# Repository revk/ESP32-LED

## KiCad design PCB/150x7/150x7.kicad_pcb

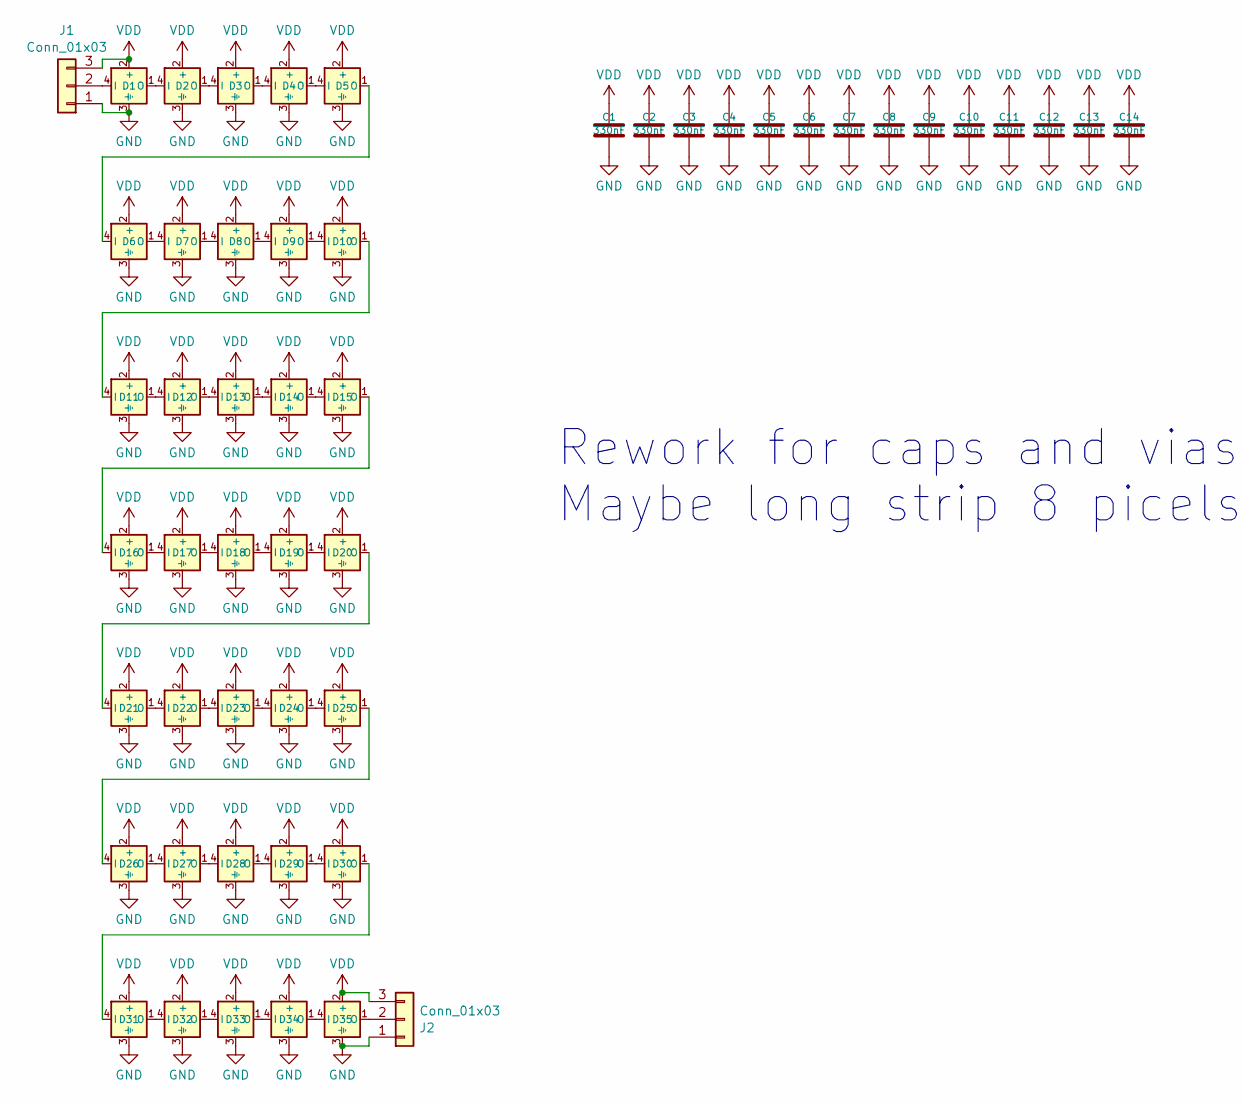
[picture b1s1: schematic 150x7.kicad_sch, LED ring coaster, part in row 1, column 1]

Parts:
C1, C2, C3, C4, C5, C6, C7, C8, C9, C10, C11, C12, C13, C14: 330nF; C_0402
D1, D2, D3, D4, D5, D6, D7, D8, D9, D10, D11, D12, D13, D14, D15, D16, D17, D18, D19, D20, D21, D22, D23, D24, D25, D26, D27, D28, D29, D30, D31, D32, D33, D34, D35: XL-1010RGBC-WS2812B; SMD1010; LCSC Part # C5349953
J1, J2: Conn_01x03; 3-PADS

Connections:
GND: C1.2, C2.2, C3.2, C4.2, C5.2, C6.2, C7.2, C8.2, C9.2, C10.2, C11.2, C12.2, C13.2, C14.2, D1.3 (⏚), D2.3 (⏚), D3.3 (⏚), D4.3 (⏚), D5.3 (⏚), D6.3 (⏚), D7.3 (⏚), D8.3 (⏚), D9.3 (⏚), D10.3 (⏚), D11.3 (⏚), D12.3 (⏚), D13.3 (⏚), D14.3 (⏚), D15.3 (⏚), D16.3 (⏚), D17.3 (⏚), D18.3 (⏚), D19.3 (⏚), D20.3 (⏚), D21.3 (⏚), D22.3 (⏚), D23.3 (⏚), D24.3 (⏚), D25.3 (⏚), D26.3 (⏚), D27.3 (⏚), D28.3 (⏚), D29.3 (⏚), D30.3 (⏚), D31.3 (⏚), D32.3 (⏚), D33.3 (⏚), D34.3 (⏚), D35.3 (⏚), J1.1, J2.1
unnamed: D1.4 (I), J1.2
unnamed: D1.1 (O), D2.4 (I)
unnamed: D2.1 (O), D3.4 (I)
unnamed: D3.1 (O), D4.4 (I)
unnamed: D4.1 (O), D5.4 (I)
unnamed: D5.1 (O), D6.4 (I)
unnamed: D6.1 (O), D7.4 (I)
unnamed: D7.1 (O), D8.4 (I)
unnamed: D8.1 (O), D9.4 (I)
unnamed: D9.1 (O), D10.4 (I)
unnamed: D10.1 (O), D11.4 (I)
unnamed: D11.1 (O), D12.4 (I)
unnamed: D12.1 (O), D13.4 (I)
unnamed: D13.1 (O), D14.4 (I)
unnamed: D14.1 (O), D15.4 (I)
unnamed: D15.1 (O), D16.4 (I)
unnamed: D16.1 (O), D17.4 (I)
unnamed: D17.1 (O), D18.4 (I)
unnamed: D18.1 (O), D19.4 (I)
unnamed: D19.1 (O), D20.4 (I)
unnamed: D20.1 (O), D21.4 (I)
unnamed: D21.1 (O), D22.4 (I)
unnamed: D22.1 (O), D23.4 (I)
unnamed: D23.1 (O), D24.4 (I)
unnamed: D24.1 (O), D25.4 (I)
unnamed: D25.1 (O), D26.4 (I)
unnamed: D26.1 (O), D27.4 (I)
unnamed: D27.1 (O), D28.4 (I)
unnamed: D28.1 (O), D29.4 (I)
unnamed: D29.1 (O), D30.4 (I)
unnamed: D30.1 (O), D31.4 (I)
unnamed: D31.1 (O), D32.4 (I)
unnamed: D32.1 (O), D33.4 (I)
unnamed: D33.1 (O), D34.4 (I)
unnamed: D34.1 (O), D35.4 (I)
unnamed: D35.1 (O), J2.2
VDD: C1.1, C2.1, C3.1, C4.1, C5.1, C6.1, C7.1, C8.1, C9.1, C10.1, C11.1, C12.1, C13.1, C14.1, D1.2 (+), D2.2 (+), D3.2 (+), D4.2 (+), D5.2 (+), D6.2 (+), D7.2 (+), D8.2 (+), D9.2 (+), D10.2 (+), D11.2 (+), D12.2 (+), D13.2 (+), D14.2 (+), D15.2 (+), D16.2 (+), D17.2 (+), D18.2 (+), D19.2 (+), D20.2 (+), D21.2 (+), D22.2 (+), D23.2 (+), D24.2 (+), D25.2 (+), D26.2 (+), D27.2 (+), D28.2 (+), D29.2 (+), D30.2 (+), D31.2 (+), D32.2 (+), D33.2 (+), D34.2 (+), D35.2 (+), J1.3, J2.3

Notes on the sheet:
Rework for caps and vias at top/bottom Maybe long strip 8 picels high to allow scrolling text

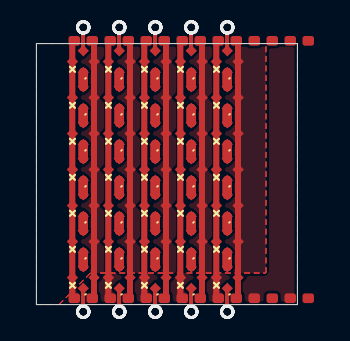
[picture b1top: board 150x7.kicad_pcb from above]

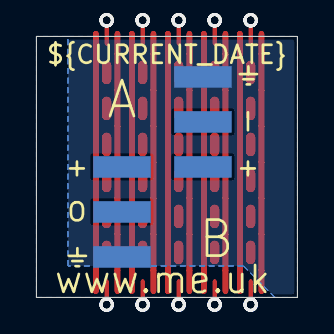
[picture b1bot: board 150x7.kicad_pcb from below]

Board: 2 copper layers, 14.5 x 14.5 mm, 51 parts (2 on the bottom side), 38 nets.

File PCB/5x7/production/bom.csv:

Designator,Footprint,Quantity,Value,LCSC Part #
"C1, C10, C2, C3, C4, C5, C6, C7, C8, C9",C_0402,10,330nF,
"D1, D10, D11, D12, D13, D14, D15, D16, D17, D18, D19, D2, D20, D21, D22, D23, D24, D25, D26, D27, D28, D29, D3, D30, D31, D32, D33, D34, D35, D4, D5, D6, D7, D8, D9",SMD1010,35,XL-1010RGBC-WS2812B,
"J1, J2",3-PADS,2,Conn_01x03,

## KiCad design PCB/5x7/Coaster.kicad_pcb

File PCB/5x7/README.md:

# 5x7

These files are for use in [KiCad](https://www.kicad.org).

## Trademark

This is an open source project, but bear in mind you cannot sell boards bearing the Andrews & Arnold Ltd name, the A&A logo, the registered trademark AJK logo, or the GS1 allocated EANs assigned to Andrews & Arnold Ltd.

## Images

*Auto generated 2025-08-12T11:30:27*

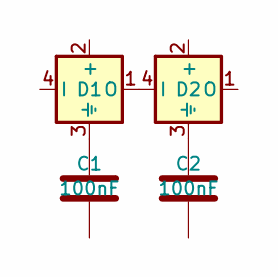
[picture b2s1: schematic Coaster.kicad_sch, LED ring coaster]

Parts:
C1, C2: 100nF; C_0201
D1, D2: XL-1010RGBC-WS2812B; SMD1010; LCSC Part # C5349953

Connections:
unnamed: D1.1 (O), D2.4 (I)
unnamed: C1.1, D1.3 (⏚)
unnamed: C2.1, D2.3 (⏚)

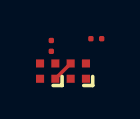
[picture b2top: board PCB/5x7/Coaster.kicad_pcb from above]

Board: 2 copper layers, 4 parts (0 on the bottom side), 3 nets.

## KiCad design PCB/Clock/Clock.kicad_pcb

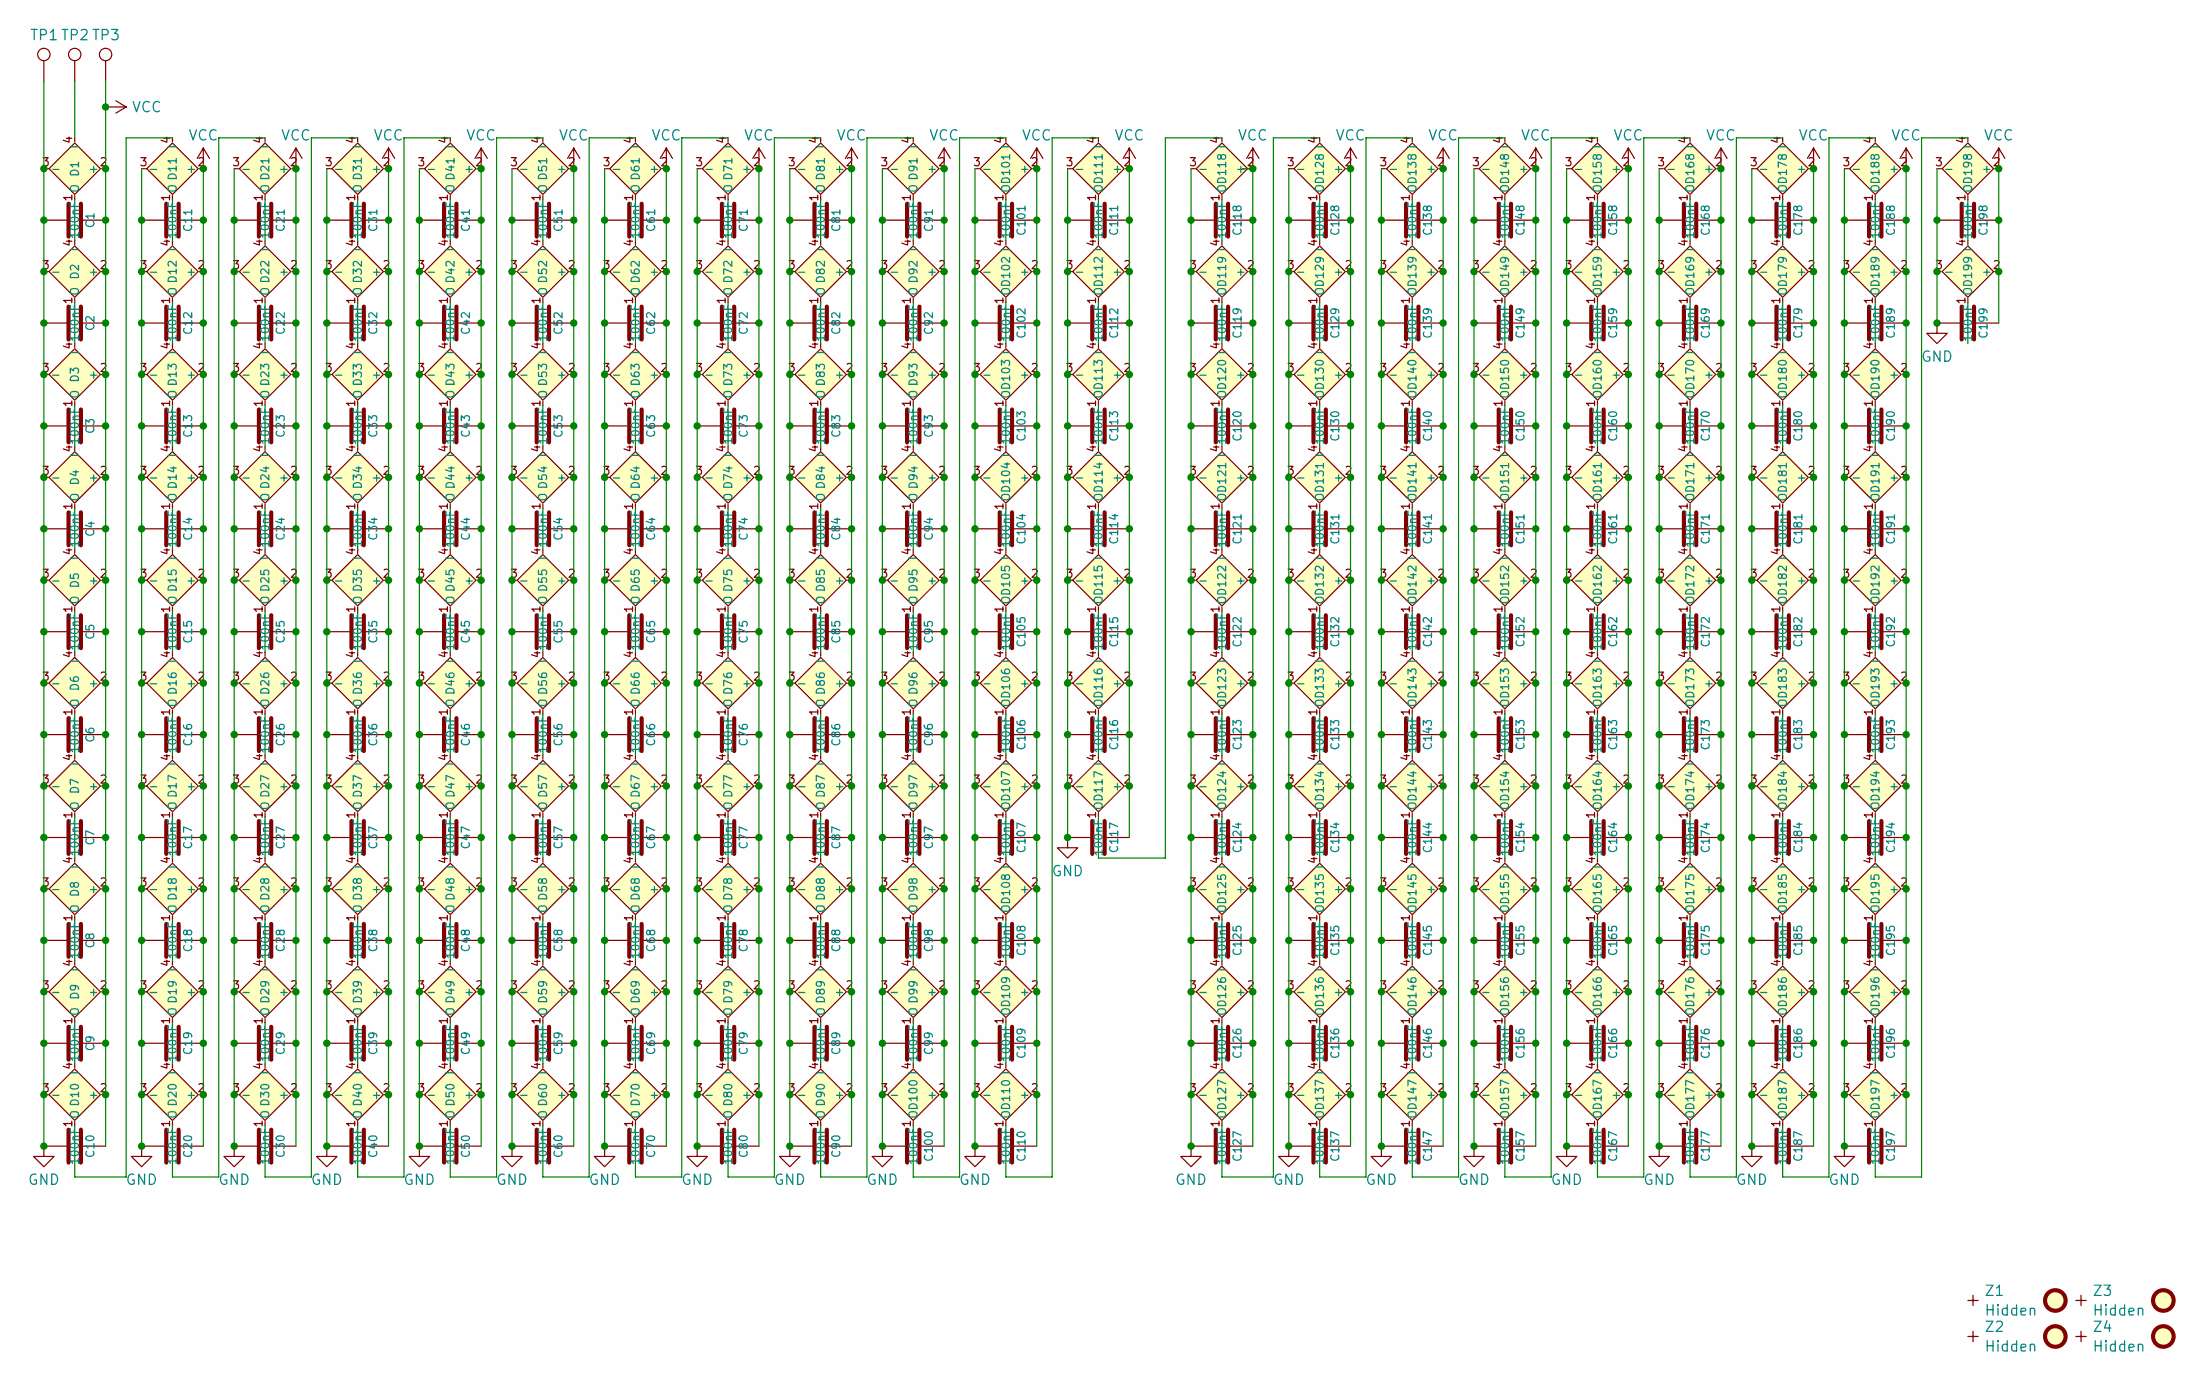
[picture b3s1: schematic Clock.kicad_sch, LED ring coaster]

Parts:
C1, C2, C3, C4, C5, C6, C7, C8, C9, C10, C11, C12, C13, C14, C15, C16, C17, C18, C19, C20, C21, C22, C23, C24, C25, C26, C27, C28, C29, C30, C31, C32, C33, C34, C35, C36, C37, C38, C39, C40, C41, C42, C43, C44, C45, C46, C47, C48, C49, C50, C51, C52, C53, C54, C55, C56, C57, C58, C59, C60, C61, C62, C63, C64, C65, C66, C67, C68, C69, C70, C71, C72, C73, C74, C75, C76, C77, C78, C79, C80, C81, C82, C83, C84, C85, C86, C87, C88, C89, C90, C91, C92, C93, C94, C95, C96, C97, C98, C99, C100, C101, C102, C103, C104, C105, C106, C107, C108, C109, C110, C111, C112, C113, C114, C115, C116, C117, C118, C119, C120, C121, C122, C123, C124, C125, C126, C127, C128, C129, C130, C131, C132, C133, C134, C135, C136, C137, C138, C139, C140, C141, C142, C143, C144, C145, C146, C147, C148, C149, C150, C151, C152, C153, C154, C155, C156, C157, C158, C159, C160, C161, C162, C163, C164, C165, C166, C167, C168, C169, C170, C171, C172, C173, C174, C175, C176, C177, C178, C179, C180, C181, C182, C183, C184, C185, C186, C187, C188, C189, C190, C191, C192, C193, C194, C195, C196, C197, C198, C199: 100nF; C_0402
D1, D2, D3, D4, D5, D6, D7, D8, D9, D10, D11, D12, D13, D14, D15, D16, D17, D18, D19, D20, D21, D22, D23, D24, D25, D26, D27, D28, D29, D30, D31, D32, D33, D34, D35, D36, D37, D38, D39, D40, D41, D42, D43, D44, D45, D46, D47, D48, D49, D50, D51, D52, D53, D54, D55, D56, D57, D58, D59, D60, D61, D62, D63, D64, D65, D66, D67, D68, D69, D70, D71, D72, D73, D74, D75, D76, D77, D78, D79, D80, D81, D82, D83, D84, D85, D86, D87, D88, D89, D90, D91, D92, D93, D94, D95, D96, D97, D98, D99, D100, D101, D102, D103, D104, D105, D106, D107, D108, D109, D110, D111, D112, D113, D114, D115, D116, D117, D118, D119, D120, D121, D122, D123, D124, D125, D126, D127, D128, D129, D130, D131, D132, D133, D134, D135, D136, D137, D138, D139, D140, D141, D142, D143, D144, D145, D146, D147, D148, D149, D150, D151, D152, D153, D154, D155, D156, D157, D158, D159, D160, D161, D162, D163, D164, D165, D166, D167, D168, D169, D170, D171, D172, D173, D174, D175, D176, D177, D178, D179, D180, D181, D182, D183, D184, D185, D186, D187, D188, D189, D190, D191, D192, D193, D194, D195, D196, D197, D198, D199: XL-1010RGBC-WS2812B; SMD1010; MPN C5349953
FID1, FID3: Fiducial; Fiducial_1mm_Mask2mm
FID2, FID4: Fiducial; Hole-Tooling
TP1: GND; Round
TP2: DIN; Round
TP3: PWR; Round
Z1, Z2, Z3, Z4: Hidden; PCB-Join1

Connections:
GND: C1.2, C2.2, C3.2, C4.2, C5.2, C6.2, C7.2, C8.2, C9.2, C10.2, C11.2, C12.2, C13.2, C14.2, C15.2, C16.2, C17.2, C18.2, C19.2, C20.2, C21.2, C22.2, C23.2, C24.2, C25.2, C26.2, C27.2, C28.2, C29.2, C30.2, C31.2, C32.2, C33.2, C34.2, C35.2, C36.2, C37.2, C38.2, C39.2, C40.2, C41.2, C42.2, C43.2, C44.2, C45.2, C46.2, C47.2, C48.2, C49.2, C50.2, C51.2, C52.2, C53.2, C54.2, C55.2, C56.2, C57.2, C58.2, C59.2, C60.2, C61.2, C62.2, C63.2, C64.2, C65.2, C66.2, C67.2, C68.2, C69.2, C70.2, C71.2, C72.2, C73.2, C74.2, C75.2, C76.2, C77.2, C78.2, C79.2, C80.2, C81.2, C82.2, C83.2, C84.2, C85.2, C86.2, C87.2, C88.2, C89.2, C90.2, C91.2, C92.2, C93.2, C94.2, C95.2, C96.2, C97.2, C98.2, C99.2, C100.2, C101.2, C102.2, C103.2, C104.2, C105.2, C106.2, C107.2, C108.2, C109.2, C110.2, C111.2, C112.2, C113.2, C114.2, C115.2, C116.2, C117.2, C118.2, C119.2, C120.2, C121.2, C122.2, C123.2, C124.2, C125.2, C126.2, C127.2, C128.2, C129.2, C130.2, C131.2, C132.2, C133.2, C134.2, C135.2, C136.2, C137.2, C138.2, C139.2, C140.2, C141.2, C142.2, C143.2, C144.2, C145.2, C146.2, C147.2, C148.2, C149.2, C150.2, C151.2, C152.2, C153.2, C154.2, C155.2, C156.2, C157.2, C158.2, C159.2, C160.2, C161.2, C162.2, C163.2, C164.2, C165.2, C166.2, C167.2, C168.2, C169.2, C170.2, C171.2, C172.2, C173.2, C174.2, C175.2, C176.2, C177.2, C178.2, C179.2, C180.2, C181.2, C182.2, C183.2, C184.2, C185.2, C186.2, C187.2, C188.2, C189.2, C190.2, C191.2, C192.2, C193.2, C194.2, C195.2, C196.2, C197.2, C198.2, C199.2, D1.3 (-), D2.3 (-), D3.3 (-), D4.3 (-), D5.3 (-), D6.3 (-), D7.3 (-), D8.3 (-), D9.3 (-), D10.3 (-), D11.3 (-), D12.3 (-), D13.3 (-), D14.3 (-), D15.3 (-), D16.3 (-), D17.3 (-), D18.3 (-), D19.3 (-), D20.3 (-), D21.3 (-), D22.3 (-), D23.3 (-), D24.3 (-), D25.3 (-), D26.3 (-), D27.3 (-), D28.3 (-), D29.3 (-), D30.3 (-), D31.3 (-), D32.3 (-), D33.3 (-), D34.3 (-), D35.3 (-), D36.3 (-), D37.3 (-), D38.3 (-), D39.3 (-), D40.3 (-), D41.3 (-), D42.3 (-), D43.3 (-), D44.3 (-), D45.3 (-), D46.3 (-), D47.3 (-), D48.3 (-), D49.3 (-), D50.3 (-), D51.3 (-), D52.3 (-), D53.3 (-), D54.3 (-), D55.3 (-), D56.3 (-), D57.3 (-), D58.3 (-), D59.3 (-), D60.3 (-), D61.3 (-), D62.3 (-), D63.3 (-), D64.3 (-), D65.3 (-), D66.3 (-), D67.3 (-), D68.3 (-), D69.3 (-), D70.3 (-), D71.3 (-), D72.3 (-), D73.3 (-), D74.3 (-), D75.3 (-), D76.3 (-), D77.3 (-), D78.3 (-), D79.3 (-), D80.3 (-), D81.3 (-), D82.3 (-), D83.3 (-), D84.3 (-), D85.3 (-), D86.3 (-), D87.3 (-), D88.3 (-), D89.3 (-), D90.3 (-), D91.3 (-), D92.3 (-), D93.3 (-), D94.3 (-), D95.3 (-), D96.3 (-), D97.3 (-), D98.3 (-), D99.3 (-), D100.3 (-), D101.3 (-), D102.3 (-), D103.3 (-), D104.3 (-), D105.3 (-)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
unnamed: D1.4 (I), TP2.1
unnamed: D1.1 (O), D2.4 (I)
unnamed: D2.1 (O), D3.4 (I)
unnamed: D3.1 (O), D4.4 (I)
unnamed: D4.1 (O), D5.4 (I)
unnamed: D5.1 (O), D6.4 (I)
unnamed: D6.1 (O), D7.4 (I)
unnamed: D7.1 (O), D8.4 (I)
unnamed: D8.1 (O), D9.4 (I)
unnamed: D9.1 (O), D10.4 (I)
unnamed: D10.1 (O), D11.4 (I)
unnamed: D11.1 (O), D12.4 (I)
unnamed: D12.1 (O), D13.4 (I)
unnamed: D13.1 (O), D14.4 (I)
unnamed: D14.1 (O), D15.4 (I)
unnamed: D15.1 (O), D16.4 (I)
unnamed: D16.1 (O), D17.4 (I)
unnamed: D17.1 (O), D18.4 (I)
unnamed: D18.1 (O), D19.4 (I)
unnamed: D19.1 (O), D20.4 (I)
unnamed: D20.1 (O), D21.4 (I)
unnamed: D21.1 (O), D22.4 (I)
unnamed: D22.1 (O), D23.4 (I)
unnamed: D23.1 (O), D24.4 (I)
unnamed: D24.1 (O), D25.4 (I)
unnamed: D25.1 (O), D26.4 (I)
unnamed: D26.1 (O), D27.4 (I)
unnamed: D27.1 (O), D28.4 (I)
unnamed: D28.1 (O), D29.4 (I)
unnamed: D29.1 (O), D30.4 (I)
unnamed: D30.1 (O), D31.4 (I)
unnamed: D31.1 (O), D32.4 (I)
unnamed: D32.1 (O), D33.4 (I)
unnamed: D33.1 (O), D34.4 (I)
unnamed: D34.1 (O), D35.4 (I)
unnamed: D35.1 (O), D36.4 (I)
unnamed: D36.1 (O), D37.4 (I)
unnamed: D37.1 (O), D38.4 (I)
unnamed: D38.1 (O), D39.4 (I)
unnamed: D39.1 (O), D40.4 (I)
unnamed: D40.1 (O), D41.4 (I)
unnamed: D41.1 (O), D42.4 (I)
unnamed: D42.1 (O), D43.4 (I)
unnamed: D43.1 (O), D44.4 (I)
unnamed: D44.1 (O), D45.4 (I)
unnamed: D45.1 (O), D46.4 (I)
unnamed: D46.1 (O), D47.4 (I)
unnamed: D47.1 (O), D48.4 (I)
unnamed: D48.1 (O), D49.4 (I)
unnamed: D49.1 (O), D50.4 (I)
unnamed: D50.1 (O), D51.4 (I)
unnamed: D51.1 (O), D52.4 (I)
unnamed: D52.1 (O), D53.4 (I)
unnamed: D53.1 (O), D54.4 (I)
unnamed: D54.1 (O), D55.4 (I)
unnamed: D55.1 (O), D56.4 (I)
unnamed: D56.1 (O), D57.4 (I)
unnamed: D57.1 (O), D58.4 (I)
unnamed: D58.1 (O), D59.4 (I)
unnamed: D59.1 (O), D60.4 (I)
unnamed: D60.1 (O), D61.4 (I)
unnamed: D61.1 (O), D62.4 (I)
unnamed: D62.1 (O), D63.4 (I)
unnamed: D63.1 (O), D64.4 (I)
unnamed: D64.1 (O), D65.4 (I)
unnamed: D65.1 (O), D66.4 (I)
unnamed: D66.1 (O), D67.4 (I)
unnamed: D67.1 (O), D68.4 (I)
unnamed: D68.1 (O), D69.4 (I)
unnamed: D69.1 (O), D70.4 (I)
unnamed: D70.1 (O), D71.4 (I)
unnamed: D71.1 (O), D72.4 (I)
unnamed: D72.1 (O), D73.4 (I)
unnamed: D73.1 (O), D74.4 (I)
unnamed: D74.1 (O), D75.4 (I)
unnamed: D75.1 (O), D76.4 (I)
unnamed: D76.1 (O), D77.4 (I)
unnamed: D77.1 (O), D78.4 (I)
unnamed: D78.1 (O), D79.4 (I)
unnamed: D79.1 (O), D80.4 (I)
unnamed: D80.1 (O), D81.4 (I)
unnamed: D81.1 (O), D82.4 (I)
unnamed: D82.1 (O), D83.4 (I)
unnamed: D83.1 (O), D84.4 (I)
unnamed: D84.1 (O), D85.4 (I)
unnamed: D85.1 (O), D86.4 (I)
unnamed: D86.1 (O), D87.4 (I)
unnamed: D87.1 (O), D88.4 (I)
unnamed: D88.1 (O), D89.4 (I)
unnamed: D89.1 (O), D90.4 (I)
unnamed: D90.1 (O), D91.4 (I)
unnamed: D91.1 (O), D92.4 (I)
unnamed: D92.1 (O), D93.4 (I)
unnamed: D93.1 (O), D94.4 (I)
unnamed: D94.1 (O), D95.4 (I)
unnamed: D95.1 (O), D96.4 (I)
unnamed: D96.1 (O), D97.4 (I)
unnamed: D97.1 (O), D98.4 (I)
unnamed: D98.1 (O), D99.4 (I)
unnamed: D99.1 (O), D100.4 (I)
unnamed: D100.1 (O), D101.4 (I)
unnamed: D101.1 (O), D102.4 (I)
unnamed: D102.1 (O), D103.4 (I)
unnamed: D103.1 (O), D104.4 (I)
unnamed: D104.1 (O), D105.4 (I)
unnamed: D105.1 (O), D106.4 (I)
unnamed: D106.1 (O), D107.4 (I)
unnamed: D107.1 (O), D108.4 (I)
unnamed: D108.1 (O), D109.4 (I)
unnamed: D109.1 (O), D110.4 (I)
unnamed: D110.1 (O), D111.4 (I)
unnamed: D111.1 (O), D112.4 (I)
unnamed: D112.1 (O), D113.4 (I)
unnamed: D113.1 (O), D114.4 (I)
unnamed: D114.1 (O), D115.4 (I)
unnamed: D115.1 (O), D116.4 (I)
unnamed: D116.1 (O), D117.4 (I)
unnamed: D117.1 (O), D118.4 (I)
unnamed: D118.1 (O), D119.4 (I)
unnamed: D119.1 (O), D120.4 (I)
unnamed: D120.1 (O), D121.4 (I)
unnamed: D121.1 (O), D122.4 (I)
unnamed: D122.1 (O), D123.4 (I)
unnamed: D123.1 (O), D124.4 (I)
unnamed: D124.1 (O), D125.4 (I)
unnamed: D125.1 (O), D126.4 (I)
unnamed: D126.1 (O), D127.4 (I)
unnamed: D127.1 (O), D128.4 (I)
unnamed: D128.1 (O), D129.4 (I)
unnamed: D129.1 (O), D130.4 (I)
unnamed: D130.1 (O), D131.4 (I)
unnamed: D131.1 (O), D132.4 (I)
unnamed: D132.1 (O), D133.4 (I)
unnamed: D133.1 (O), D134.4 (I)
unnamed: D134.1 (O), D135.4 (I)
unnamed: D135.1 (O), D136.4 (I)
unnamed: D136.1 (O), D137.4 (I)
unnamed: D137.1 (O), D138.4 (I)
unnamed: D138.1 (O), D139.4 (I)
unnamed: D139.1 (O), D140.4 (I)
unnamed: D140.1 (O), D141.4 (I)
unnamed: D141.1 (O), D142.4 (I)
unnamed: D142.1 (O), D143.4 (I)
unnamed: D143.1 (O), D144.4 (I)
unnamed: D144.1 (O), D145.4 (I)
unnamed: D145.1 (O), D146.4 (I)
unnamed: D146.1 (O), D147.4 (I)
unnamed: D147.1 (O), D148.4 (I)
unnamed: D148.1 (O), D149.4 (I)
unnamed: D149.1 (O), D150.4 (I)
unnamed: D150.1 (O), D151.4 (I)
unnamed: D151.1 (O), D152.4 (I)
unnamed: D152.1 (O), D153.4 (I)
unnamed: D153.1 (O), D154.4 (I)
unnamed: D154.1 (O), D155.4 (I)
unnamed: D155.1 (O), D156.4 (I)
unnamed: D156.1 (O), D157.4 (I)
unnamed: D157.1 (O), D158.4 (I)
unnamed: D158.1 (O), D159.4 (I)
unnamed: D159.1 (O), D160.4 (I)
unnamed: D160.1 (O), D161.4 (I)
unnamed: D161.1 (O), D162.4 (I)
unnamed: D162.1 (O), D163.4 (I)
unnamed: D163.1 (O), D164.4 (I)
unnamed: D164.1 (O), D165.4 (I)
unnamed: D165.1 (O), D166.4 (I)
unnamed: D166.1 (O), D167.4 (I)
unnamed: D167.1 (O), D168.4 (I)
unnamed: D168.1 (O), D169.4 (I)
unnamed: D169.1 (O), D170.4 (I)
unnamed: D170.1 (O), D171.4 (I)
unnamed: D171.1 (O), D172.4 (I)
unnamed: D172.1 (O), D173.4 (I)
unnamed: D173.1 (O), D174.4 (I)
unnamed: D174.1 (O), D175.4 (I)
unnamed: D175.1 (O), D176.4 (I)
unnamed: D176.1 (O), D177.4 (I)
unnamed: D177.1 (O), D178.4 (I)
unnamed: D178.1 (O), D179.4 (I)
unnamed: D179.1 (O), D180.4 (I)
unnamed: D180.1 (O), D181.4 (I)
unnamed: D181.1 (O), D182.4 (I)
unnamed: D182.1 (O), D183.4 (I)
unnamed: D183.1 (O), D184.4 (I)
unnamed: D184.1 (O), D185.4 (I)
unnamed: D185.1 (O), D186.4 (I)
unnamed: D186.1 (O), D187.4 (I)
unnamed: D187.1 (O), D188.4 (I)
unnamed: D188.1 (O), D189.4 (I)
unnamed: D189.1 (O), D190.4 (I)
unnamed: D190.1 (O), D191.4 (I)
unnamed: D191.1 (O), D192.4 (I)
unnamed: D192.1 (O), D193.4 (I)
unnamed: D193.1 (O), D194.4 (I)
unnamed: D194.1 (O), D195.4 (I)
unnamed: D195.1 (O), D196.4 (I)
unnamed: D196.1 (O), D197.4 (I)
unnamed: D197.1 (O), D198.4 (I)
unnamed: D198.1 (O), D199.4 (I)
VCC: C1.1, C2.1, C3.1, C4.1, C5.1, C6.1, C7.1, C8.1, C9.1, C10.1, C11.1, C12.1, C13.1, C14.1, C15.1, C16.1, C17.1, C18.1, C19.1, C20.1, C21.1, C22.1, C23.1, C24.1, C25.1, C26.1, C27.1, C28.1, C29.1, C30.1, C31.1, C32.1, C33.1, C34.1, C35.1, C36.1, C37.1, C38.1, C39.1, C40.1, C41.1, C42.1, C43.1, C44.1, C45.1, C46.1, C47.1, C48.1, C49.1, C50.1, C51.1, C52.1, C53.1, C54.1, C55.1, C56.1, C57.1, C58.1, C59.1, C60.1, C61.1, C62.1, C63.1, C64.1, C65.1, C66.1, C67.1, C68.1, C69.1, C70.1, C71.1, C72.1, C73.1, C74.1, C75.1, C76.1, C77.1, C78.1, C79.1, C80.1, C81.1, C82.1, C83.1, C84.1, C85.1, C86.1, C87.1, C88.1, C89.1, C90.1, C91.1, C92.1, C93.1, C94.1, C95.1, C96.1, C97.1, C98.1, C99.1, C100.1, C101.1, C102.1, C103.1, C104.1, C105.1, C106.1, C107.1, C108.1, C109.1, C110.1, C111.1, C112.1, C113.1, C114.1, C115.1, C116.1, C117.1, C118.1, C119.1, C120.1, C121.1, C122.1, C123.1, C124.1, C125.1, C126.1, C127.1, C128.1, C129.1, C130.1, C131.1, C132.1, C133.1, C134.1, C135.1, C136.1, C137.1, C138.1, C139.1, C140.1, C141.1, C142.1, C143.1, C144.1, C145.1, C146.1, C147.1, C148.1, C149.1, C150.1, C151.1, C152.1, C153.1, C154.1, C155.1, C156.1, C157.1, C158.1, C159.1, C160.1, C161.1, C162.1, C163.1, C164.1, C165.1, C166.1, C167.1, C168.1, C169.1, C170.1, C171.1, C172.1, C173.1, C174.1, C175.1, C176.1, C177.1, C178.1, C179.1, C180.1, C181.1, C182.1, C183.1, C184.1, C185.1, C186.1, C187.1, C188.1, C189.1, C190.1, C191.1, C192.1, C193.1, C194.1, C195.1, C196.1, C197.1, C198.1, C199.1, D1.2 (+), D2.2 (+), D3.2 (+), D4.2 (+), D5.2 (+), D6.2 (+), D7.2 (+), D8.2 (+), D9.2 (+), D10.2 (+), D11.2 (+), D12.2 (+), D13.2 (+), D14.2 (+), D15.2 (+), D16.2 (+), D17.2 (+), D18.2 (+), D19.2 (+), D20.2 (+), D21.2 (+), D22.2 (+), D23.2 (+), D24.2 (+), D25.2 (+), D26.2 (+), D27.2 (+), D28.2 (+), D29.2 (+), D30.2 (+), D31.2 (+), D32.2 (+), D33.2 (+), D34.2 (+), D35.2 (+), D36.2 (+), D37.2 (+), D38.2 (+), D39.2 (+), D40.2 (+), D41.2 (+), D42.2 (+), D43.2 (+), D44.2 (+), D45.2 (+), D46.2 (+), D47.2 (+), D48.2 (+), D49.2 (+), D50.2 (+), D51.2 (+), D52.2 (+), D53.2 (+), D54.2 (+), D55.2 (+), D56.2 (+), D57.2 (+), D58.2 (+), D59.2 (+), D60.2 (+), D61.2 (+), D62.2 (+), D63.2 (+), D64.2 (+), D65.2 (+), D66.2 (+), D67.2 (+), D68.2 (+), D69.2 (+), D70.2 (+), D71.2 (+), D72.2 (+), D73.2 (+), D74.2 (+), D75.2 (+), D76.2 (+), D77.2 (+), D78.2 (+), D79.2 (+), D80.2 (+), D81.2 (+), D82.2 (+), D83.2 (+), D84.2 (+), D85.2 (+), D86.2 (+), D87.2 (+), D88.2 (+), D89.2 (+), D90.2 (+), D91.2 (+), D92.2 (+), D93.2 (+), D94.2 (+), D95.2 (+), D96.2 (+), D97.2 (+), D98.2 (+), D99.2 (+), D100.2 (+), D101.2 (+), D102.2 (+), D103.2 (+), D104.2 (+), D105.2 (+)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

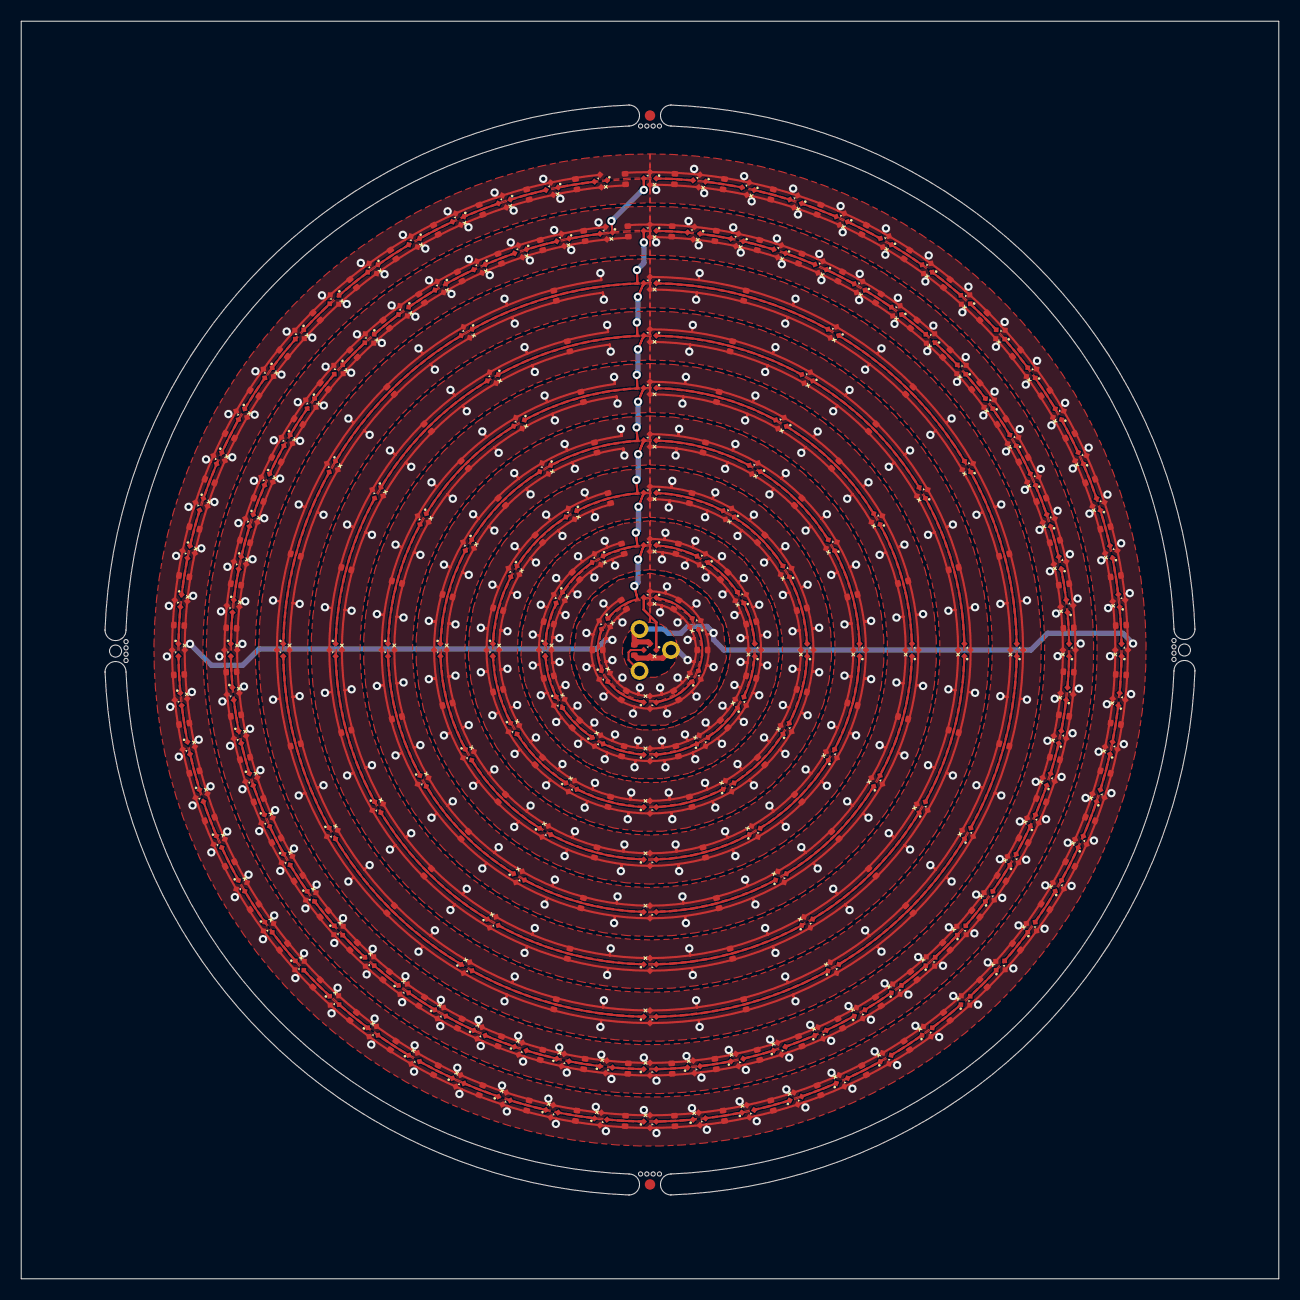
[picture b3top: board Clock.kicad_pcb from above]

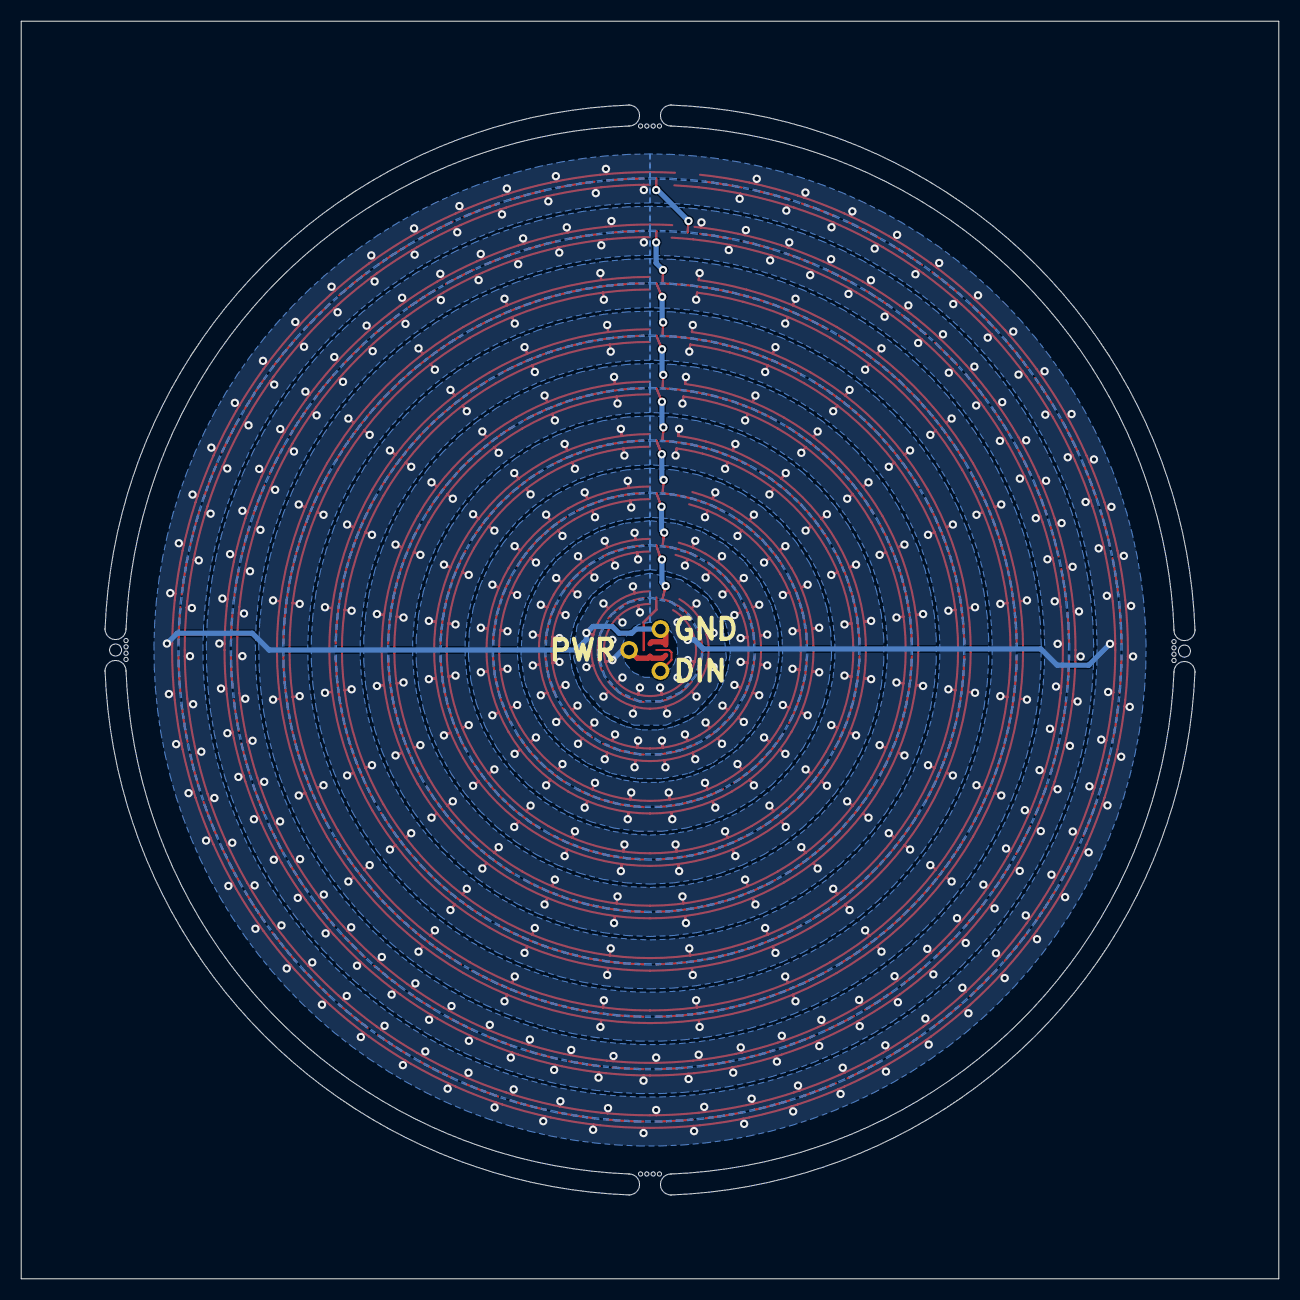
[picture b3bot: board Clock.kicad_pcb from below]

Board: 2 copper layers, 120.0 x 120.0 mm, 409 parts (3 on the bottom side), 201 nets.

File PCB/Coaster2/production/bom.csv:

Designator,Footprint,Quantity,Value,LCSC Part #
"C1, C10, C100, C101, C102, C103, C104, C105, C106, C107, C108, C109, C11, C110, C111, C112, C113, C114, C115, C116, C117, C118, C119, C12, C120, C121, C122, C123, C124, C129, C13, C132, C14, C15, C16, C17, C18, C19, C2, C20, C21, C22, C23, C24, C25, C26, C27, C28, C29, C3, C30, C31, C32, C33, C34, C35, C36, C37, C38, C39, C4, C40, C41, C42, C43, C44, C45, C46, C47, C48, C49, C5, C50, C51, C52, C53, C54, C55, C56, C57, C58, C59, C6, C60, C61, C62, C63, C64, C65, C66, C67, C68, C69, C7, C70, C71, C72, C73, C74, C75, C76, C77, C78, C79, C8, C80, C81, C82, C83, C84, C85, C86, C87, C88, C89, C9, C90, C91, C92, C93, C94, C95, C96, C97, C98, C99",C_0402,126,100nF,
C130,C_0603,1,22uF,
C131,CP_EIA-3528-21_Kemet-B,1,220uF Tant,C122649
"C133, C135, C136",C_0603,3,10uF 35V,C194427
C134,C_0402,1,1uF,
C137,C_0603_,1,10uF 35V,C194427
C138,C_0603_,1,10uF 6.3V,C1691
C139,C_0603_,1,100nF,
"D1, D10, D100, D101, D102, D103, D104, D105, D106, D107, D108, D109, D11, D110, D111, D112, D113, D114, D115, D116, D117, D118, D119, D12, D120, D121, D122, D123, D124, D13, D14, D15, D16, D17, D18, D19, D2, D20, D21, D22, D23, D24, D25, D26, D27, D28, D29, D3, D30, D31, D32, D33, D34, D35, D36, D37, D38, D39, D4, D40, D41, D42, D43, D44, D45, D46, D47, D48, D49, D5, D50, D51, D52, D53, D54, D55, D56, D57, D58, D59, D6, D60, D61, D62, D63, D64, D65, D66, D67, D68, D69, D7, D70, D71, D72, D73, D74, D75, D76, D77, D78, D79, D8, D80, D81, D82, D83, D84, D85, D86, D87, D88, D89, D9, D90, D91, D92, D93, D94, D95, D96, D97, D98, D99",SMD1010,124,XL-1010RGBC-WS2812B,C5349953
J3,USB-C-Socket-H,1,USB-C-Socket-H,C709357
L1,L_4x4_,1,10uH,
R1,R_0402,1,10K,
R2,R_0402_,1,124k,
R3,R_0402_,1,39k2,
R4,R_0402_,1,1M,
"R5, R6",R_0402,2,5K1,
U1,ICS43434_MEMS_Mic,1,ICS43434_MEMS_Mic,C5656610
U2,ESP32-S3-MINI-1,1,ESP32-S3-MINI-1,C3013941
U3,SOT-23-6-MD8942,1,MD8942,C2684786

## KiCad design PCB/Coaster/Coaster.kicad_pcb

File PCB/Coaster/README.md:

# Coaster

These files are for use in [KiCad](https://www.kicad.org).

## Trademark

This is an open source project, but bear in mind you cannot sell boards bearing the Andrews & Arnold Ltd name, the A&A logo, the registered trademark AJK logo, or the GS1 allocated EANs assigned to Andrews & Arnold Ltd.

## Images

*Auto generated 2025-08-12T11:38:05*

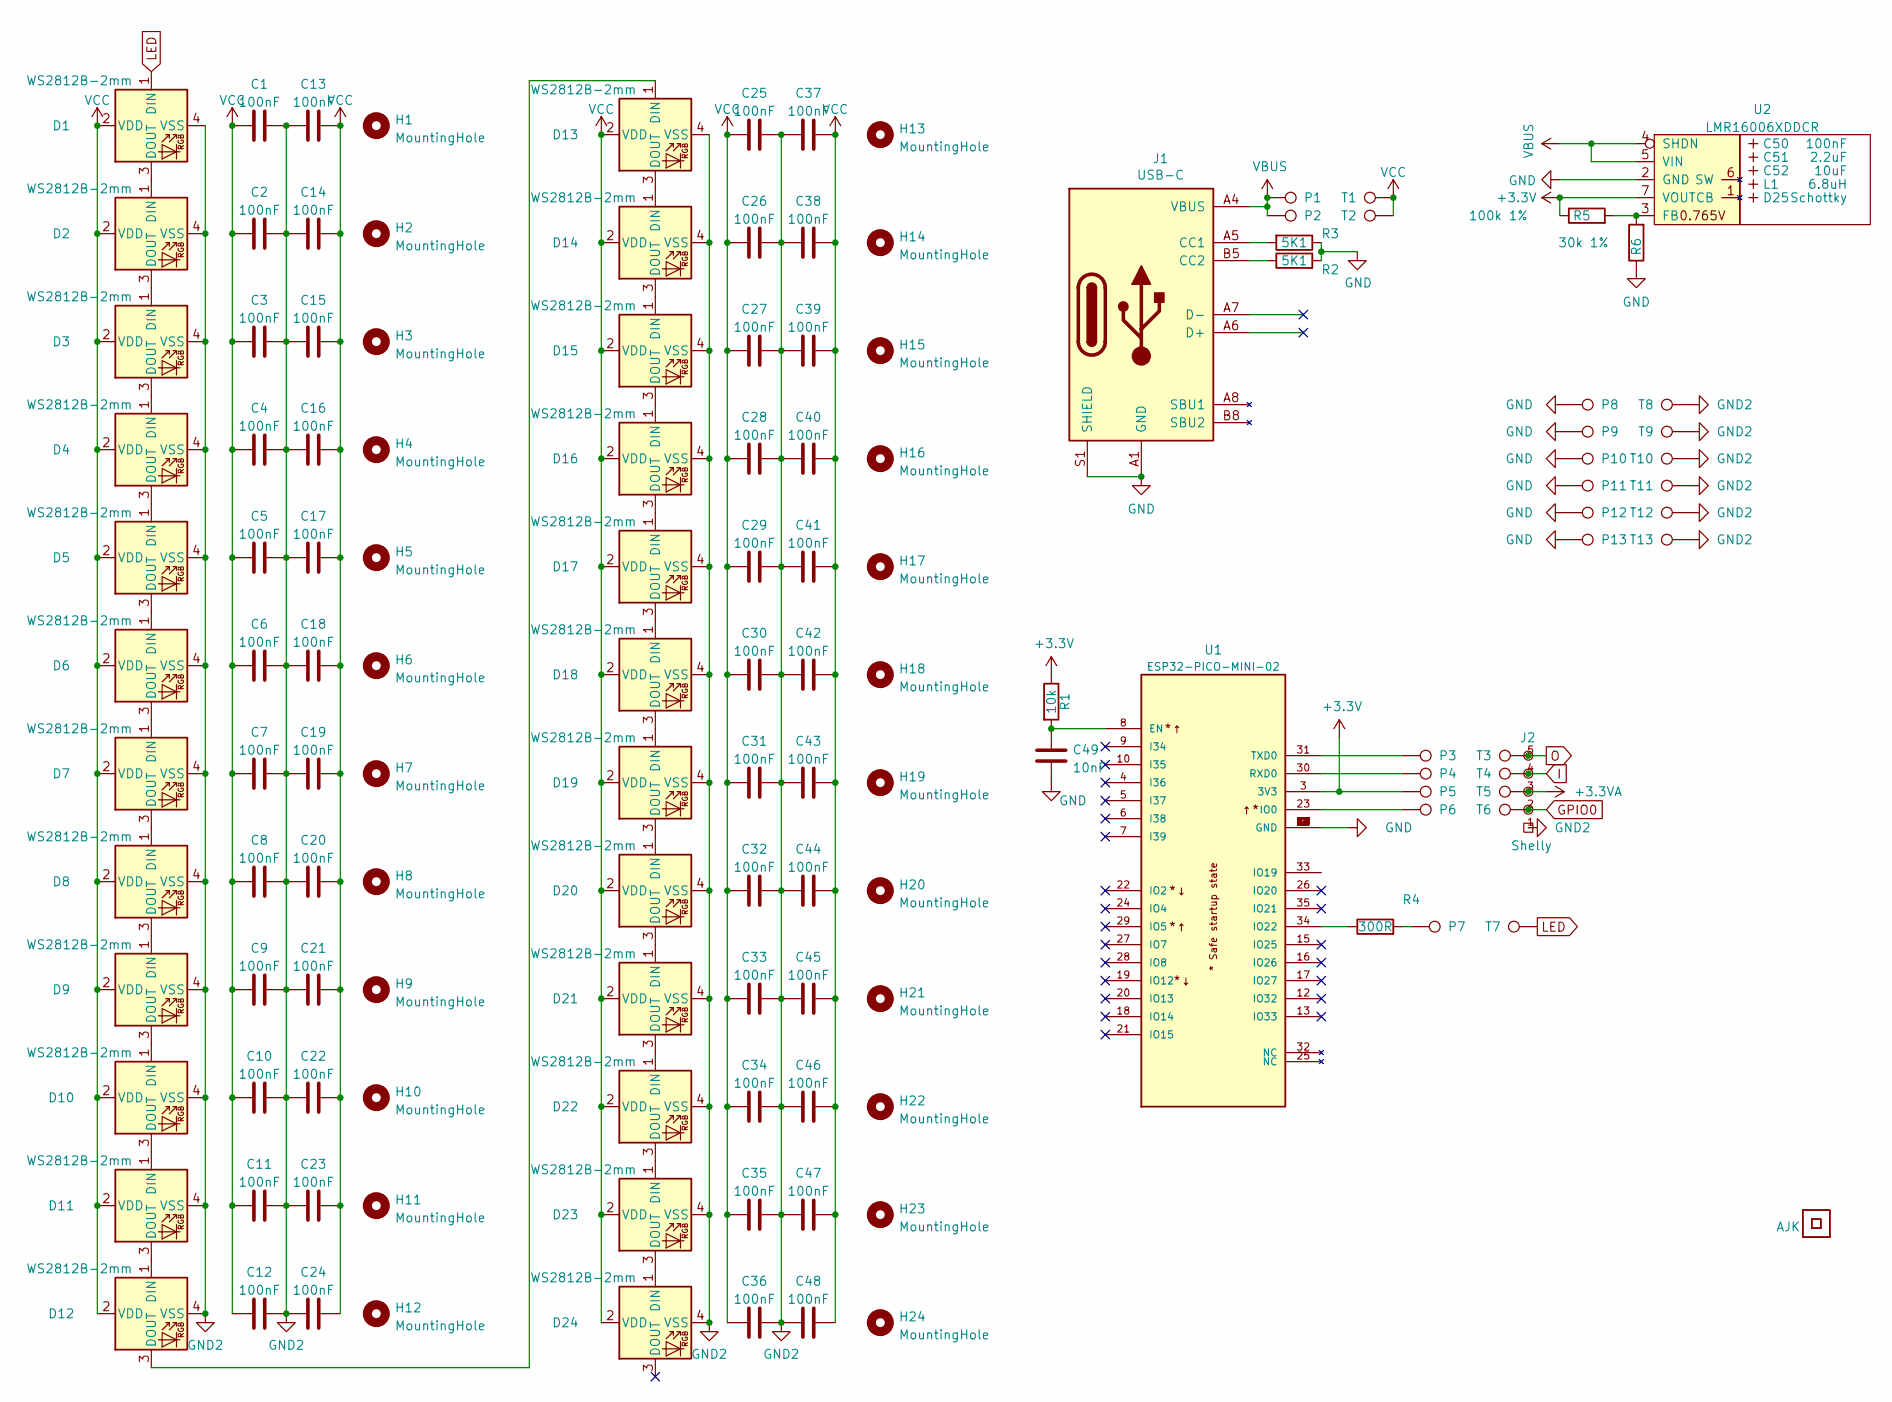
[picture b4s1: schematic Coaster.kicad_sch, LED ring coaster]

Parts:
C1, C2, C3, C4, C5, C6, C7, C8, C9, C10, C11, C12, C13, C14, C15, C16, C17, C18, C19, C20, C21, C22, C23, C24, C25, C26, C27, C28, C29, C30, C31, C32, C33, C34, C35, C36, C37, C38, C39, C40, C41, C42, C43, C44, C45, C46, C47, C48: 100nF; C_0603
C49: 10nF; C_0603_1608Metric
C50: 100nF; C_0603_; MPN C30926
C51: 2.2uF; C_0805_; MPN C19110
C52: 10uF; C_0805_; MPN C17024
D1, D2, D3, D4, D5, D6, D7, D8, D9, D10, D11, D12, D13, D14, D15, D16, D17, D18, D19, D20, D21, D22, D23, D24: WS2812B-2mm; SMD2020; MPN C784564
D25: Schottky; D_1206_; MPN C143805
H1, H2, H3, H4, H5, H6, H7, H8, H9, H10, H11, H12, H13, H14, H15, H16, H17, H18, H19, H20, H21, H22, H23, H24: MountingHole; LEDHOLE
J1: USB-C; USC16-TR; MPN C709357
J2: Shelly
L1: 6.8uH; L_4x4_; MPN C354575
Logo1: AJK
P1, P2, P3, P4, P5, P6, P7, P8, P9, P10, P11, P12, P13: TestPoint; PAD
R1: 10k; R_0603
R2, R3: 5K1; R_0603
R4: 300R; R_0603
R5: 100k 1%; R_0603; MPN C14675
R6: 30k 1%; R_0603; MPN C100001
T1, T2, T3, T4, T5, T6, T7, T8, T9, T10, T11, T12, T13: TestPoint; PAD-LINK
U1: ESP32-PICO-MINI-02; PARTREV v1.0
U2: LMR16006XDDCR; SOT-23-Thin-6-Reg; Part No LMR16006XDDCR
U3: QR; QR-LED

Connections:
+3.3V: P5.1, R1.1, R5.1, U1.3 (3V3), U2.7 (VOUT)
+3.3VA: J2.3 (3V3), T5.1
GND: C49.1, J1.A1 (GND), J1.A12 (GND), J1.B1 (GND), J1.B12 (GND), J1.S1 (SHIELD), P8.1, P9.1, P10.1, P11.1, P12.1, P13.1, R2.1, R3.2, R6.1, U1.1 (GND), U1.2 (GND), U1.11 (GND), U1.14 (GND), U1.36 (GND), U1.37 (GND), U1.38 (GND), U1.39 (GND), U1.40 (GND), U1.41 (GND), U1.42 (GND), U1.43 (GND), U1.44 (GND), U1.45 (GND), U1.46 (GND), U1.47 (GND), U1.48 (GND), U1.49 (GND), U1.50 (GND), U1.51 (GND), U1.52 (GND), U1.53 (GND), U2.2 (GND)
GND2: C1.2, C2.2, C3.2, C4.2, C5.2, C6.2, C7.2, C8.2, C9.2, C10.2, C11.2, C12.2, C13.2, C14.2, C15.2, C16.2, C17.2, C18.2, C19.2, C20.2, C21.2, C22.2, C23.2, C24.2, C25.2, C26.2, C27.2, C28.2, C29.2, C30.2, C31.2, C32.2, C33.2, C34.2, C35.2, C36.2, C37.2, C38.2, C39.2, C40.2, C41.2, C42.2, C43.2, C44.2, C45.2, C46.2, C47.2, C48.2, D1.4 (VSS), D2.4 (VSS), D3.4 (VSS), D4.4 (VSS), D5.4 (VSS), D6.4 (VSS), D7.4 (VSS), D8.4 (VSS), D9.4 (VSS), D10.4 (VSS), D11.4 (VSS), D12.4 (VSS), D13.4 (VSS), D14.4 (VSS), D15.4 (VSS), D16.4 (VSS), D17.4 (VSS), D18.4 (VSS), D19.4 (VSS), D20.4 (VSS), D21.4 (VSS), D22.4 (VSS), D23.4 (VSS), D24.4 (VSS), J2.1 (GND), T8.1, T9.1, T10.1, T11.1, T12.1, T13.1
GPIO0: J2.2 (0), T6.1
I: J2.4 (Rx), T4.1
LED: D1.1 (DIN), T7.1
unnamed: D1.3 (DOUT), D2.1 (DIN)
unnamed: D2.3 (DOUT), D3.1 (DIN)
unnamed: D3.3 (DOUT), D4.1 (DIN)
unnamed: D4.3 (DOUT), D5.1 (DIN)
unnamed: D5.3 (DOUT), D6.1 (DIN)
unnamed: D6.3 (DOUT), D7.1 (DIN)
unnamed: D7.3 (DOUT), D8.1 (DIN)
unnamed: D8.3 (DOUT), D9.1 (DIN)
unnamed: D9.3 (DOUT), D10.1 (DIN)
unnamed: D10.3 (DOUT), D11.1 (DIN)
unnamed: D11.3 (DOUT), D12.1 (DIN)
unnamed: D12.3 (DOUT), D13.1 (DIN)
unnamed: D13.3 (DOUT), D14.1 (DIN)
unnamed: D14.3 (DOUT), D15.1 (DIN)
unnamed: D15.3 (DOUT), D16.1 (DIN)
unnamed: D16.3 (DOUT), D17.1 (DIN)
unnamed: D17.3 (DOUT), D18.1 (DIN)
unnamed: D18.3 (DOUT), D19.1 (DIN)
unnamed: D19.3 (DOUT), D20.1 (DIN)
unnamed: D20.3 (DOUT), D21.1 (DIN)
unnamed: D21.3 (DOUT), D22.1 (DIN)
unnamed: D22.3 (DOUT), D23.1 (DIN)
unnamed: D23.3 (DOUT), D24.1 (DIN)
unnamed: J1.A5 (CC1), R2.2
unnamed: J1.B5 (CC2), R3.1
unnamed: P7.1, R4.2
unnamed: C49.2, R1.2, U1.8 (EN)
unnamed: P6.1, U1.23 (IO0)
unnamed: R4.1, U1.34 (IO22)
unnamed: P4.1, U1.30 (RXD0)
unnamed: P3.1, U1.31 (TXD0)
unnamed: R5.2, R6.2, U2.3 (FB)
O: J2.5 (Tx), T3.1
VBUS: J1.A4 (VBUS), J1.A9 (VBUS), J1.B4 (VBUS), J1.B9 (VBUS), P1.1, P2.1, U2.4 (SHDN), U2.5 (VIN)
VCC: C1.1, C2.1, C3.1, C4.1, C5.1, C6.1, C7.1, C8.1, C9.1, C10.1, C11.1, C12.1, C13.1, C14.1, C15.1, C16.1, C17.1, C18.1, C19.1, C20.1, C21.1, C22.1, C23.1, C24.1, C25.1, C26.1, C27.1, C28.1, C29.1, C30.1, C31.1, C32.1, C33.1, C34.1, C35.1, C36.1, C37.1, C38.1, C39.1, C40.1, C41.1, C42.1, C43.1, C44.1, C45.1, C46.1, C47.1, C48.1, D1.2 (VDD), D2.2 (VDD), D3.2 (VDD), D4.2 (VDD), D5.2 (VDD), D6.2 (VDD), D7.2 (VDD), D8.2 (VDD), D9.2 (VDD), D10.2 (VDD), D11.2 (VDD), D12.2 (VDD), D13.2 (VDD), D14.2 (VDD), D15.2 (VDD), D16.2 (VDD), D17.2 (VDD), D18.2 (VDD), D19.2 (VDD), D20.2 (VDD), D21.2 (VDD), D22.2 (VDD), D23.2 (VDD), D24.2 (VDD), T1.1, T2.1
